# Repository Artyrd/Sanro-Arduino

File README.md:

# Sanro - Arduino
（このREADME.mdは日本語訳版があります、README_JP.mdをご覧ください、訳は完璧には程遠いですが）  
Hardware program of the game Taiko Sanro.

## What is This Program

Music game fans from East Asia countries are most probable to know a famous game called Taiko No Tatsujin ([太鼓の達人](http://taiko-ch.net/)), developed by [Bandai Namco Entertainment](http://bandainamcoent.co.jp/).

This open-source program aims to help you develop your own **hardware taiko** at home, just like how you play taiko in arcade halls.

*This program is for personal and non-commercial use only. You may design your own taiko and have fun, but you may NOT distribute your product to the public.*

## Features

* **Full support for the PC game Taiko-san Jiro (太鼓さん次郎).** Actually, any app/game/emulator using keyboards as input is supported.
* **Force-sensitive.** I am also developing a new open-source game called Taiko Sanro that can support this feature.
* **Supports dense inputs such as rolling.**

*In one word, your taiko will perform exactly the same as the arcade version if you configure the program well enough! :D*

## Prerequisites

Because this is a DIY project, you should have some basic  electronic engineering knowledge about connecting microprocessors with jumper wires on a breadboard. **Soldering techniques, however, are NOT required.**

## Getting Started

It might take you a few days to assembly and configure your own taiko device. The microprocessor chips are cheap, though, you can buy them from wherever you want.

### Preparation

Almost all of these things have alternatives, now I will show you what I used:

* [Arduino Micro](http://i.imgur.com/lXqnpJ9.jpg) module x 1
* [KEYES K-036](http://i.imgur.com/gUWnUCc.png) microphone module x 4
* Breadboard x 1
* A few jumper wires
* Micro USB cable x 1
* [Arduino IDE](https://www.arduino.cc/en/Main/Software)

And miscellaneous stuffs like:

* Thick wood plank x 4, best to be [shaped like this](http://i.imgur.com/va20eVn.jpg)
* Foamed plastics to connect and fixate the wood
* Superglue
* Other electronical tools like screw drivers and multimeters, etc.

A few things to note:

1. Any Arduino modules with ATmega32u4 chips or Due and Zero boards are supported. Arduino Micro is the cheapest one, though.
2. Using a breadboard is a low-cost option, but it is not the best/stablest choice. There is a PCB blueprint that allows you to print the integrated board and solder up. For details, please see "Making the PCB" part below.
3. You can also design and build your own microphones modules, just make sure you know how to connect them to your Arduino module.
4. Thick, solid, dense and heavy wood is the best choice, while plywood, particleboard and medium-density fiberboard (MDF) are fragile at their edges and can be easily damaged. For better experience, you should cut the planks with the shapes shown in [the picture](http://i.imgur.com/va20eVn.jpg). If you don't have the cutting tools and want it easier, just prepare 4 planks.

### Connecting the Parts

The scheme is quite simple. You don't even need any extra resistors or capacitors. **All you need are jumper wires.**

Each microphone module has 4 pins, and we only need 3 of them (`A0`, `+`, and `G`). Connect their `A0` outputs to Arduino Micro's `A0`~`A3` inputs, then connect their `+` pins together with module's `5V` pin, then the `G` pins together to the ground. Use the following picture if you have any problems.

(Picture to be uploaded)

### (Optional) Making the PCB

To make the PCB, you can either DIY or ask local PCB manufacturer for help. If you choose DIY, you should prepare a few more things, including:

* 2.2 x 1.6 inches Empty PCB x 1
* Thermal transfer paper x 1
* Laser printer x 1
* Standard 4-pin header x 4
* Thermal transfer machine (or clothes iron)
* Etchant
* Soldering tools

Detailed process to make the PCB is totally off-topic, and you may need [this video](https://www.youtube.com/watch?v=mv7Y0A9YeUc) to help you. I have included the required printable board file `sanro.eps` in the `Eagle/sanro-arduino` folder. You can also download the scheme and board files and edit them by yourself with the [Eagle Software](http://www.cadsoftusa.com/download-eagle/).

### Uploading the Program to the Board

1. Download and install [Arduino IDE](https://www.arduino.cc/en/Main/Software).
2. Create a folder and put the source files (`sanro.ino` and `cache.h`) into it.
3. Connect your Arduino Micro to your computer with a USB cable. The driver installation should be automatic, but if you have any questions about it, [check this official guide](https://www.arduino.cc/en/Guide/ArduinoLeonardoMicro#toc8).
4. Open the `sanro` project in Arduino IDE.
5. Select "Board" - "Arduino/Genuino Micro" from the menu.
6. Compile and upload the program.

## Configuration

***WARNING: Because of the deviations between the microphones and the installation of the planks, you will spend much time adjusting the hardware and the parameters in the program. Be patient, there are lots of tries-and-errors up ahead.***

### Hardware

Literally there is only 2 things you need to do:

1. Glue each microphone to the wood plank
2. Fixate the wood planks onto the foamed plastics 

However, the problem is how you do them. There are some major criteria when doing this job:

* Attach the microphone to the plank as close/tight as possible
* Seal the microphone to isolate it from outside noises
* Don't let the planks contact each other

To accomplish them, you can remove the filter cover of the microphone receiver, then attach the receiver face (the microphones are usually cylindrical, like [the ones that I used in this project](http://i.imgur.com/gUWnUCc.png)) tightly to the surface of the plank, and seal it with superglue. In this way, the soundwave from the plank can be directly transmitted to the microphone, loud and clear. Also, noises and soundwave from nearby planks can be reduced to the minimum.

Also, please note that there is a potentiometer on the KEYES module, which is used to set the quiescent operating point (Q-point) of the microphone. Although I have implemented algorithms to eliminate the bias caused by unequal Q-point of each microphone, **it is better to adjust the potentiometer manually and keep the Q-points at approximately the same level.** To do this, you may need to contact your microphone provider.

### Parameters in the Program

All you need to change is the `LIGHT_THRES` and the `HEAVY_THRES`, according to your microphone configuration.

The codes are short and self-explanatory, and if you need help understanding them, please refer to the "About the Algorithm" part.

(To be completed)

## About the Algorithm

The algorithm in the program is simple, and there are still much more to be optimized. All pull requests are welcomed!

In short, the signal processing job can be divided into 4 calculating steps after acquiring the samples from the analog inputs:

1. Calculate the derivative
2. Calculate the power of the waveform
3. Calculate the convolution of the power
4. Find the peak of the power convolution and compare it with the thresholds to see if there is a light or heavy hit

This picture shows the algorithm in a clearer way:

(Picture to be uploaded)

Step 1 is to elinimate the difference of Q-point, which makes it easier and more accurate to calculate the power of the waveform.

Step 2, calculating the power of the waveform, can also enhance the signal to noise ratio (SNR), which can further eliminate the noises. `LIGHT_THRES` is also used here to cut the low-power noises out.

Step 3 is to "polish" the power curve to make it more like a sequence of hit pulses, which makes it easier to find the power peak.

For Arduino microprocessors, the executing time for each loop is not stable - the processor always executes the instructions as fast as it can. Onece the loop ends, it immediately starts the next loop. This is extremely bad for sampling sounds. Therefore, the program implements a simple sampling frequency control mechanism to restrict the sampling frequency to no more than 1,000Hz.

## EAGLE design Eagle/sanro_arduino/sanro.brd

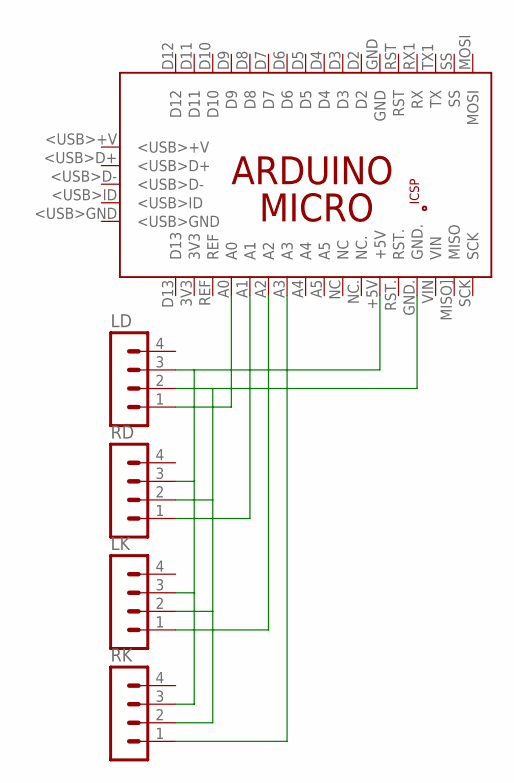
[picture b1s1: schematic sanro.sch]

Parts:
LD: MA04-1
LK: MA04-1
PCB1: ARDUINO_MICRO
RD: MA04-1
RK: MA04-1

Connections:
unnamed: LD.1, PCB1.A0
unnamed: PCB1.A1, RD.1
unnamed: LK.1, PCB1.A2
unnamed: PCB1.A3, RK.1
unnamed: LD.2, LK.2, PCB1.GND., RD.2, RK.2
unnamed: LD.3, LK.3, PCB1.+5V, RD.3, RK.3

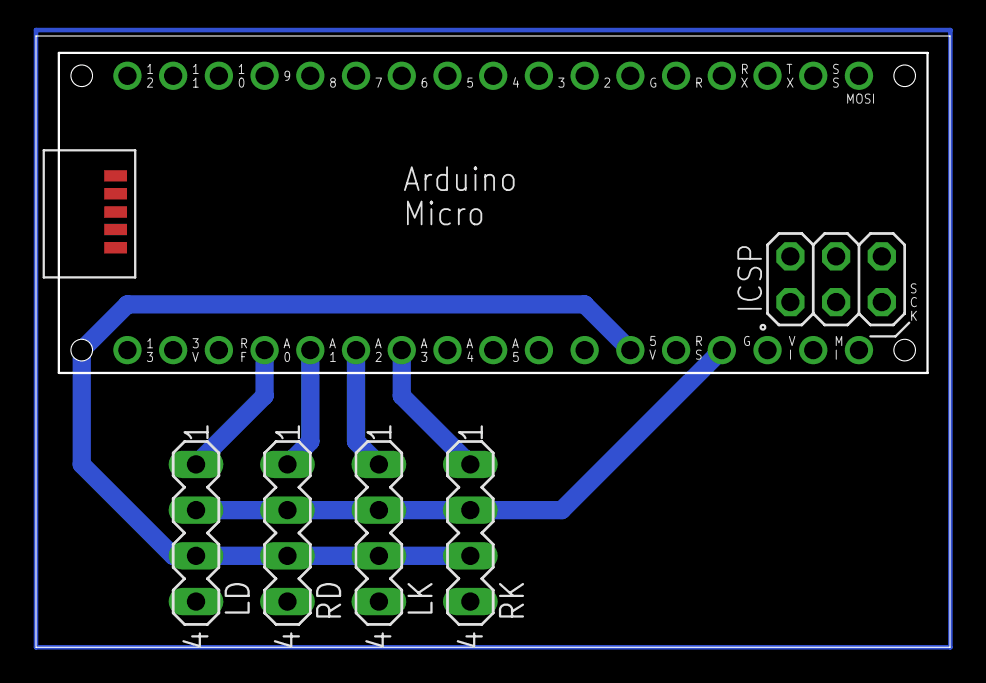
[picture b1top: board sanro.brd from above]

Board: 2 copper layers, 50.7 x 33.8 mm, 5 parts (0 on the bottom side), 6 nets.

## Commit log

2022-04-08 moved lastTime re-assignment to after delay
2022-04-08 delay algorithm uses cycle time (so that forced frequency can be modified), remapped input keys
2022-04-10 changed cache.h
2022-04-19 disabled don triggers when same side ka is hit
2022-04-19 started adding LuiCat's switch support
2022-04-29 works with nintendo switch ft saer debel
2022-04-29 removed need to break during ns button pressing
2022-05-12 implemented toggle
